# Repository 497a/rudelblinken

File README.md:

# rudelblinken

Synced blinking catears

## Notes

Less of a Readme, more a unstructured braindump

## Updating all cat ears nearby

_If builders built buildings the way programmers wrote programs, then the first woodpecker that came along would destroy civilization._ - Gerald Weinberg

Sometimes you may want to update all cat ears. This is the (for now untested) protocol I would use:

1. Make sure you have jaguar version `v1.41.0` installed. Running `nix develop` in this repo will install it for you.

2. Setup an WiFi AP on channel 6 with the SSID: `rudelctrl` and the password `22po7gl334ai`. On linux you can use the following command:

```
sudo create_ap --freq-band 2.4 -c 6 YOUR_WIFI_DEVICE YOUR_WIFI_DEVICE 'rudelctrl' '22po7gl334ai'
```

I usually use a second laptop for that.

3. Connect your machine to the AP

4. Make sure UDP port 1990 is open on your machine

5. Turn on your own cat ears and run `jag scan` to verify you can find them and figure out their name. Then try `jag container install rudelblinken main.toit -d NAME_OF_YOUR_CATEARS` to verify that everything works on your device.

6. Run around with your devices like a mad cat and run `make install-all` repeatedly to update all cat ears in range

## Hardware

rudelblinken is based on ESP32-C3 supermicro boards. Each device controls a single color LED strip. This should keep the hardware setup quite, simple requiring only a esp board, a mosfet, an LED strip and some wires for each node.

For now I just blink the builtin LEDs of the boards, more detail will follow once I built the actual hardware.

## Software stack

The software for rudelblinken is written in [toit](https://toitlang.org/), a high-level language designed for ESP32 programming. The devices are flashed with the [jaguar](https://github.com/toitlang/jaguar) firmware, which makes it possible to deploy toit programs over WiFi. Each device tries to connect to a hotspot named `rudelctrl` with the password `22po7gl334ai`. It is important that you use channel 6. You can start an AP with that configuration using `make start-ap`. You can also set your own WiFi and password when flashing the devices.

The devices communicate using the [ESP-NOW](https://docs.espressif.com/projects/esp-idf/en/stable/esp32/api-reference/network/esp_now.html) protocol. ESP-NOW was choosen over WiFi, because WiFi is not connectionless. ESP-NOW was choosen over BLE, because it seems like the only way for connectionless communication. There are BLE advertisments but the ESP does not have an API to send a single advertisment, only to start sending in a given interval. ESP-NOW uses WiFi vendor-specific action frames. As it is using the WiFi hardware, it is limited to operating on the same channel as our WiFi connection. To receive messages from other devices they need to use the same channel. For rudelblinken this is channel 6. There are some limitations, when using ESP-NOW and WiFi at the same time.

For this reason toit does not allow ESP-NOW and WiFi to coexist. To fix this issue we use a [custom envelope](https://github.com/zebreus/toit-envelope-with-espnow) with a patched version of toit, that has removed the checks for coexistance and is patched so the ESP-NOW channel follows the WiFi channel and defaults to 6. So when you are flashing your esps with jaguar you need to use the custom envelope. The custom envelope also has a patch that lets any program access the name of the device. To built the patched firmware and flash a device with it run `make flash-DEVICENAME`.

Flashed devices will attempt to connect with the control AP and can be programmed via WiFi. Use `make run-all` to run the main program on all connected devices. Use `make install-all` to install the main program over multiple reboots on all devices. `make uninstall-all` to uninstall on all devices.

## Build instructions

You can find some basic instructions on how to build your own rudelblinken cat ears based on a ESP32-C3 supermini board at https://md.darmstadt.ccc.de/rudelblinken-mrmcd

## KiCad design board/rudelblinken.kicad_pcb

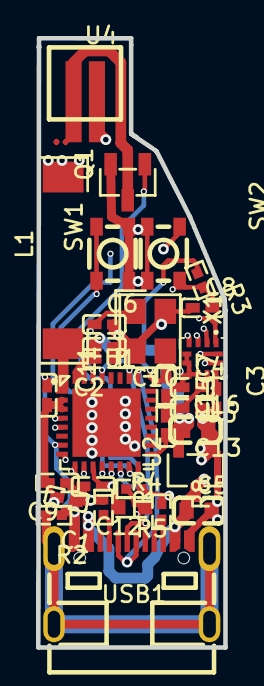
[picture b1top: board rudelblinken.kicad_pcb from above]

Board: 4 copper layers, 10.4 x 33.8 mm, 31 parts (0 on the bottom side), 22 nets.

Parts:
C1, C2, C13: 10uF; C0402
C3, C4, C9, C12, C15: 100nF; C0402
C5, C16: 22uF; C0603
C6, C7: 22pF; C0402
C8, C10, C11: 1uF; C0402
L1: AN9520-245; ANT-SMD_L9.5-W2.1
Q1: AO3400A; SOT-23-3_L2.9-W1.3-P1.90-LS2.4-BR
R2: 1MΩ; R0402
R3, R5: 10kΩ; R0402
R4: ALS-PT19-315C/L177/TR8; SENSORS-SMD_ALS-PT19
R7, R8: 5.1kΩ; R0402
SW1, SW2: K2-1830UQ-A4DW-06; KEY-SMD_4P-L3.0-W2.6-P1.80-LS3.5
U1: ESP32-C3FH4; QFN-32_L5.0-W5.0-P0.50-TL-EP3.7
U2: XC6206P332MR; SOT-23-3_L2.9-W1.6-P1.90-LS2.8-BR
U4: LED strip; LED STRIP 4MM
U5: LIS2DH12TR; LGA-12_L2.0-W2.0-P0.50-BL
USB1: MC-107D; USB-C-SMD_MC-107D
X1: 40MHz; CRYSTAL-SMD_4P-L3.2-W2.5-BL

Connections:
3.3V: C1.2, C2.2, C3.1, C4.2, C9.2, C10.2, C11.2, C12.1, C13.2, C15.2, C16.1, R3.1, R4.1, U1.2, U1.3, U1.11, U1.17, U1.31, U1.32, U2.2, U5.9, U5.10
ACC_CLK: U1.5, U5.1
ACC_CS: U1.4, U5.2
ACC_INT1: U1.12, U5.12
ACC_INT2: U1.13, U5.11
ACC_SDI: U1.9, U5.4
ACC_SDO: U1.10, U5.3
AMBIENT: R4.2, R5.2, U1.8
ANTENNA: L1.1, U1.1
BOOT: SW1.1, SW1.2, U1.15
CC1: R7.2, USB1.A5
CC2: R8.2, USB1.B5
D+: U1.26, USB1.A6, USB1.B6
D-: U1.25, USB1.A7, USB1.B7
GND: C1.1, C2.1, C3.2, C4.1, C5.2, C6.2, C7.2, C8.1, C9.1, C10.1, C11.1, C12.2, C13.1, C15.1, C16.2, L1.2, Q1.2, R2.1, R5.1, R7.1, R8.1, SW1.3, SW1.4, SW2.3, SW2.4, U1.33, U2.1, U5.5, U5.6, U5.7, U5.8, USB1.A1B12, USB1.B1A12, X1.2, X1.4
LED: Q1.1, U1.14
RESET: C8.2, R3.2, SW2.1, SW2.2, U1.7
SHIELD: R2.2, USB1.0
U4_1: Q1.3, U4.1
VBUS: C5.1, U2.3, U4.2, USB1.A4B9, USB1.B4A9
XTAL_N: C7.1, U1.29, X1.3
XTAL_P: C6.1, U1.30, X1.1

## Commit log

2024-09-09 Add nix flake with environment
2024-09-11 Improve development environment
2024-09-11 Write some blinking code
2024-09-11 First prototype for synchronized blinking
2024-09-12 Add target to start a preconfigured AP
2024-09-12 Start writing documentation
2024-09-12 Add some more documentation
2024-09-16 Add some scripts for experiments
2024-09-17 Split synchronization implementation
2024-09-17 Add target for flashing devices
2024-09-17 Document flashing process
2024-09-22 Import board from easyeda
2024-09-22 Add kicad and easyeda2kicad
2024-09-22 Organize schematics for kicad
2024-09-22 Fix kicad
2024-09-22 Add kicad autosave files to gitignore
2024-09-22 Download kicad parts from lcsc
2024-09-30 Add support for the ambient light sensor
2024-10-03 Refactor shit
2024-10-03 Adjust led brightness curve
2024-10-03 Fix led calibration
2024-10-03 Add two experiments
2024-10-03 Change blinking to sinus wave
2024-10-03 Add ambient light sensor support
2024-10-03 Pin jaguar version
2024-10-03 Make communication resilient against unknown packages
2024-10-03 Add dom mode
2024-10-05 Wrap communication code in a catch block
2024-10-05 Wrap all tasks in catch blocks
2024-10-05 Remove kicad from the nix shell
2024-10-05 Add prebuilt patched firmware to the repository
2024-10-05 Add a protocol for updating all cat ears nearby
2024-10-05 Revert accidental change
2024-10-05 Add license
